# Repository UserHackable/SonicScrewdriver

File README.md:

## LiPolyRGB 

### Board dimensions

* (160000, 70000) original units
* (1.6000, 0.7000) inches
* (40.6400, 17.7800) mm

| Front | Back |
| --- | --- |
|  |  |

## LiPolySonicScrewdriver 

### Board dimensions

* (190000, 47500) original units
* (1.9000, 0.4750) inches
* (48.2600, 12.0650) mm

| Front | Back |
| --- | --- |
|  |  |

## sonic_screwdriver 

### Board dimensions

* (139950, 29960) original units
* (1.3995, 0.2996) inches
* (35.5473, 7.6098) mm

| Front | Back |
| --- | --- |
|  |  |

## sonic_screwdriver_lipo 

### Board dimensions

* (139950, 29960) original units
* (1.3995, 0.2996) inches
* (35.5473, 7.6098) mm

| Front | Back |
| --- | --- |
|  |  |

## SonicScrewdriverThru 

### Board dimensions

* (249951, 49961) original units
* (2.4995, 0.4996) inches
* (63.4876, 12.6901) mm

| Front | Back |
| --- | --- |
|  |  |

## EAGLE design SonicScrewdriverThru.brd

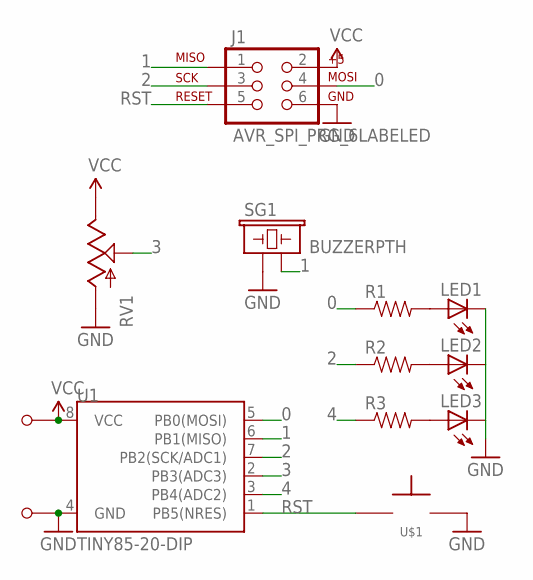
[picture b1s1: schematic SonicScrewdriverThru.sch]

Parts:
J1: AVR_SPI_PRG_6LABELED; 2X3-NS
LED1, LED2, LED3: LEDOVAL; LED-OVAL
R1, R2, R3: RESISTORAXIAL-0.3; AXIAL-0.3
RV1: POTTHUMB; THUMB
SG1: BUZZERPTH; BUZZER-12MM
U1: TINY85-20-DIP; DIP08
U$1: TAC_SPST_NO
U$2, U$3: M1; M1_NO_STRAIN

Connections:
0: J1.4, R1.P$1 (1), U1.5 (PB0(MOSI))
1: J1.1, SG1.- (2), U1.6 (PB1(MISO))
2: J1.3, R2.P$1 (1), U1.7 (PB2(SCK/ADC1))
3: RV1.B (S), U1.2 (PB3(ADC3))
4: R3.P$1 (1), U1.3 (PB4(ADC2))
GND: J1.6, LED1.CATHODE (C), LED2.CATHODE (C), LED3.CATHODE (C), RV1.A, SG1.+ (1), U1.4 (GND), U$1.P$2, U$3.P$1
unnamed: LED1.ANODE (A), R1.P$2 (2)
unnamed: LED2.ANODE (A), R2.P$2 (2)
unnamed: LED3.ANODE (A), R3.P$2 (2)
RST: J1.5, U1.1 (PB5(NRES)), U$1.P$1
VCC: J1.2, RV1.C (E), U1.8 (VCC), U$2.P$1

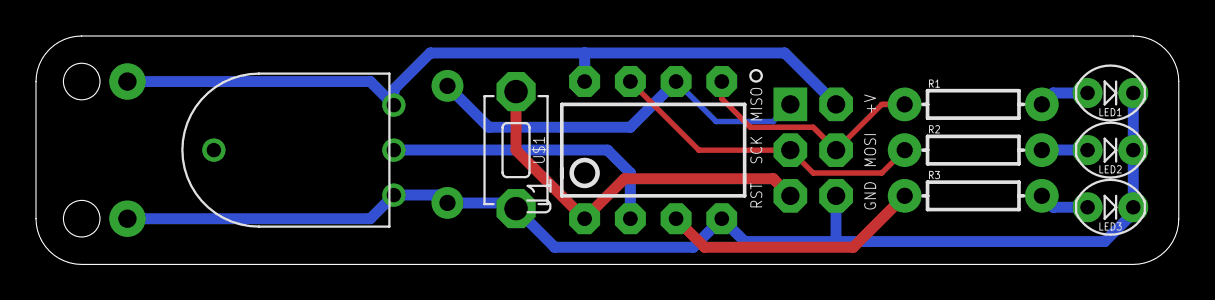
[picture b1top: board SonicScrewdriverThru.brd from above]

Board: 2 copper layers, 63.5 x 12.7 mm, 13 parts (1 on the bottom side), 11 nets.

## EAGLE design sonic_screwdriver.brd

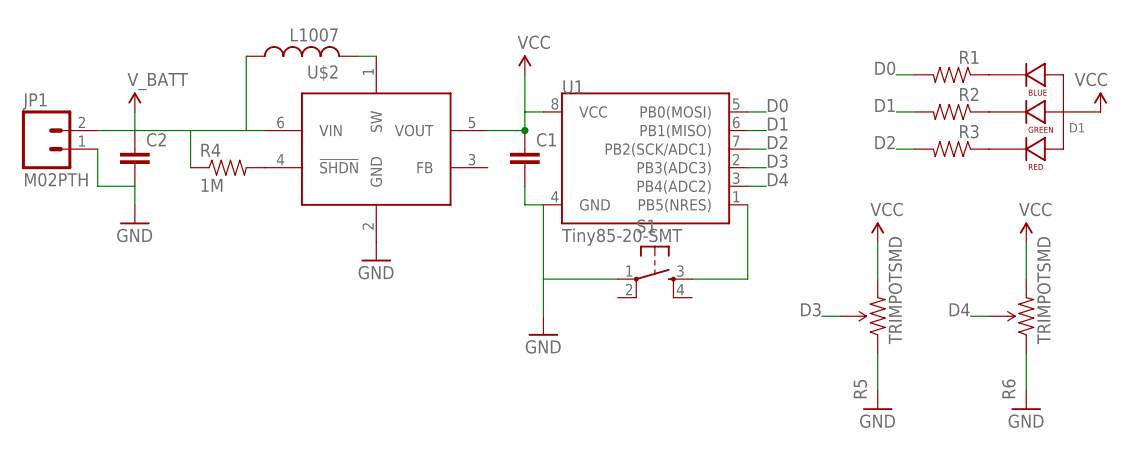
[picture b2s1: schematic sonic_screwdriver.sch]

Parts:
C1, C2: CAP1206; 1206
D1: LED-RGB-CA-THRUEDGE; LED-RGB-EDGE
JP1: M02PTH; 1X02
R1, R2, R3: RESISTOR0805-RES; 0805
R4: 1M; 0805
R5, R6: TRIMPOTSMD; TRIMPOT-3MM
S1: TAC_SWITCHSMD; TACTILE-SWITCH-SMD
U1: Tiny85-20-SMT; SO08-EIAJ
U$1: AAT1217; TSOT-23-6
U$2: L1007

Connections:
D0: R1.2, U1.5 (PB0(MOSI))
D1: R2.2, U1.6 (PB1(MISO))
D2: R3.2, U1.7 (PB2(SCK/ADC1))
D3: R5.2 (WIPER), U1.2 (PB3(ADC3))
D4: R6.2 (WIPER), U1.3 (PB4(ADC2))
GND: C1.2, C2.2, JP1.1, R5.1 (CCW), R6.1 (CCW), S1.1, U1.4 (GND), U$1.2 (GND)
unnamed: D1.4 (BLUE_CATHODE), R1.1
unnamed: D1.3 (GREEN_CATHODE), R2.1
unnamed: D1.1 (RED_CATHODE), R3.1
unnamed: R4.2, U$1.4 (!SHDN)
unnamed: U$1.1 (SW), U$2.P$2 (2)
RESET: S1.3, U1.1 (PB5(NRES))
VCC: C1.1, D1.2 (ANODE), R5.3 (CW), R6.3 (CW), U1.8 (VCC), U$1.5 (VOUT)
V_BATT: C2.1, JP1.2, R4.1, U$1.6 (VIN), U$2.P$1 (1)

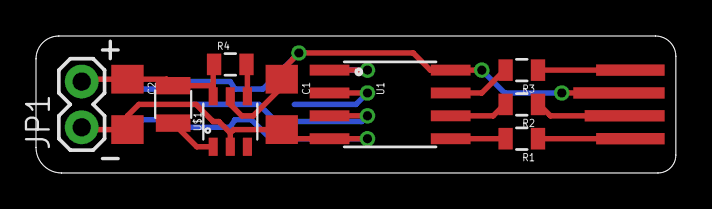
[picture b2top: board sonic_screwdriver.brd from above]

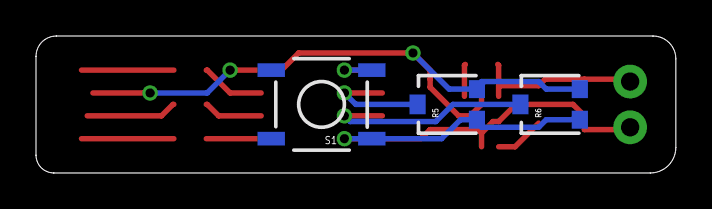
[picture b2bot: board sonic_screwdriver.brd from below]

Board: 2 copper layers, 35.5 x 7.6 mm, 14 parts (3 on the bottom side), 14 nets.

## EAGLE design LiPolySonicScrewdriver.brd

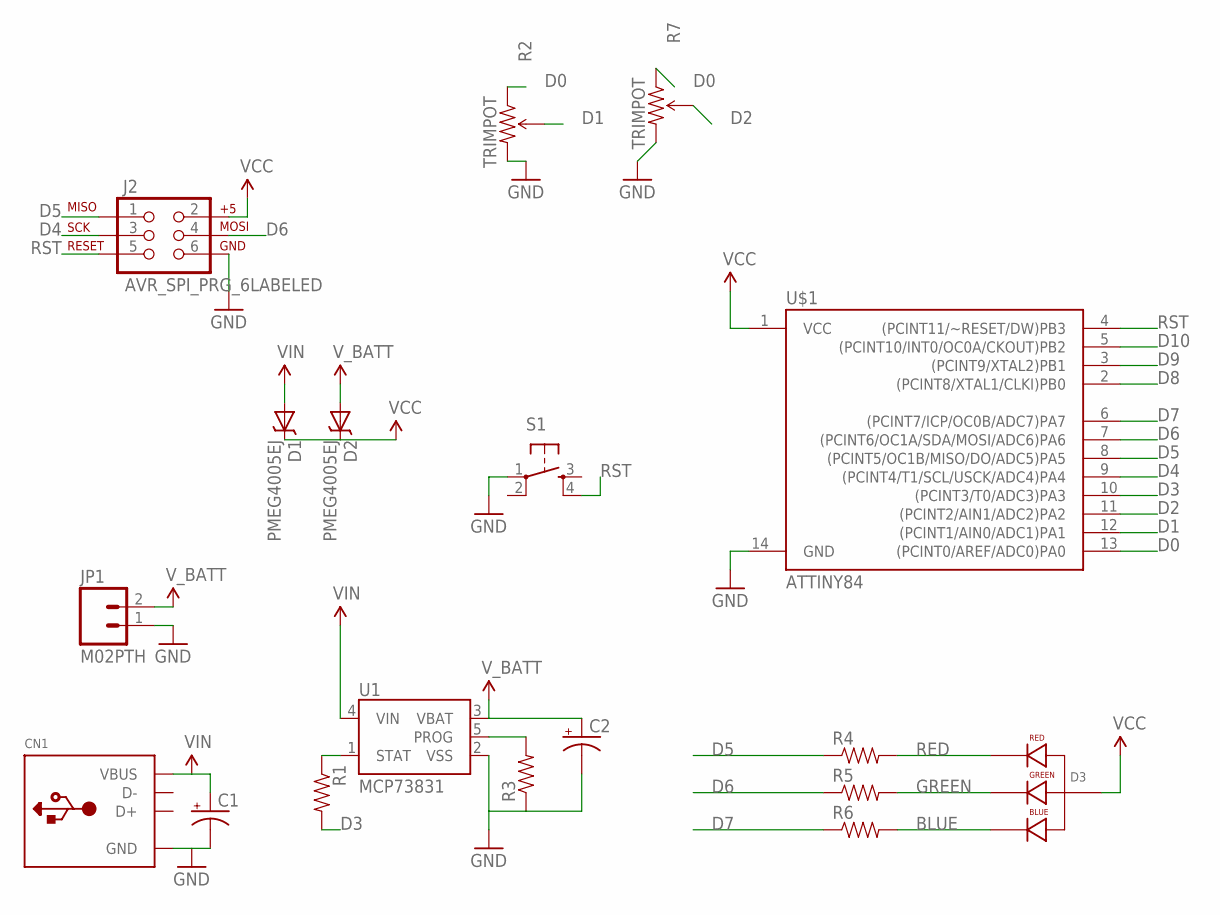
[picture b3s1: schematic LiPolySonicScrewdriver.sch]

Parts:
C1, C2: CAP_POL1206; EIA3216
CN1: USB_TYPEAPCB; USBA_PCB
D1, D2: PMEG4005EJ; SOD-323
D3: LED-RGB-CA-THRUEDGE; LED-RGB-EDGE
J2: AVR_SPI_PRG_6LABELED; 2X3-NS
JP1: M02PTH; 1X02
R1, R3: RESISTOR0805-RES; 0805
R2, R7: TRIMPOT; TRIMPOT-5MM-V2
R4, R5, R6: RESISTOR1206; 1206
S1: TAC_SWITCHSMD; TACTILE-SWITCH-SMD
U1: MCP73831; SOT23-5
U$1: ATTINY84; SO14

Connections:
BLUE: D3.4 (BLUE_CATHODE), R6.2
D0: R2.A (CCW), R7.A (CCW), U$1.13 ((PCINT0/AREF/ADC0)PA0)
D1: R2.B (WIPER), U$1.12 ((PCINT1/AIN0/ADC1)PA1)
D2: R7.B (WIPER), U$1.11 ((PCINT2/AIN1/ADC2)PA2)
D3: R1.2, U$1.10 ((PCINT3/T0/ADC3)PA3)
D4: J2.3, U$1.9 ((PCINT4/T1/SCL/USCK/ADC4)PA4)
D5: J2.1, R4.1, U$1.8 ((PCINT5/OC1B/MISO/DO/ADC5)PA5)
D6: J2.4, R5.1, U$1.7 ((PCINT6/OC1A/SDA/MOSI/ADC6)PA6)
D7: R6.1, U$1.6 ((PCINT7/ICP/OC0B/ADC7)PA7)
D8: U$1.2 ((PCINT8/XTAL1/CLKI)PB0)
D9: U$1.3 ((PCINT9/XTAL2)PB1)
D10: U$1.5 ((PCINT10/INT0/OC0A/CKOUT)PB2)
GND: C1.C (-), C2.C (-), CN1.GND, J2.6, JP1.1, R2.C (CW), R3.1, R7.C (CW), S1.1, U1.2 (VSS), U$1.14 (GND)
GREEN: D3.3 (GREEN_CATHODE), R5.2
unnamed: R3.2, U1.5 (PROG)
RED: D3.1 (RED_CATHODE), R4.2
RST: J2.5, S1.4, U$1.4 ((PCINT11/~RESET/DW)PB3)
STAT: R1.1, U1.1 (STAT)
VCC: D1.C, D2.C, D3.2 (ANODE), J2.2, U$1.1 (VCC)
VIN: C1.A (+), CN1.VCC (VBUS), D1.A, U1.4 (VIN)
V_BATT: C2.A (+), D2.A, JP1.2, U1.3 (VBAT)

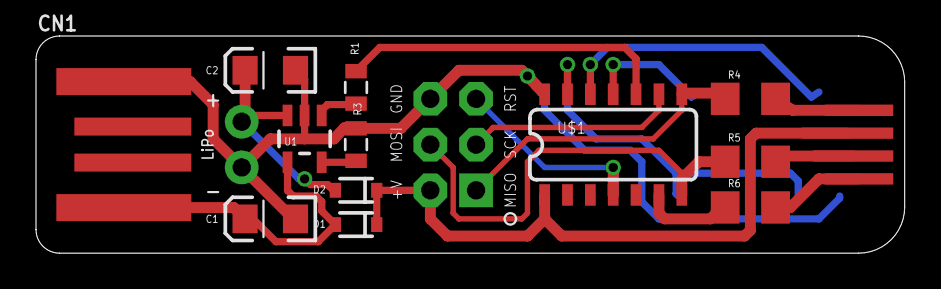
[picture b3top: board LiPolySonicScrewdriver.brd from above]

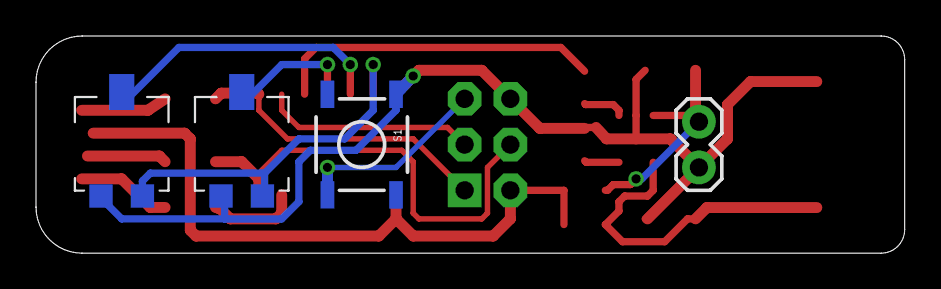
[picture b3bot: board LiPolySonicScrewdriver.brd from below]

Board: 2 copper layers, 48.3 x 12.1 mm, 18 parts (4 on the bottom side), 18 nets.

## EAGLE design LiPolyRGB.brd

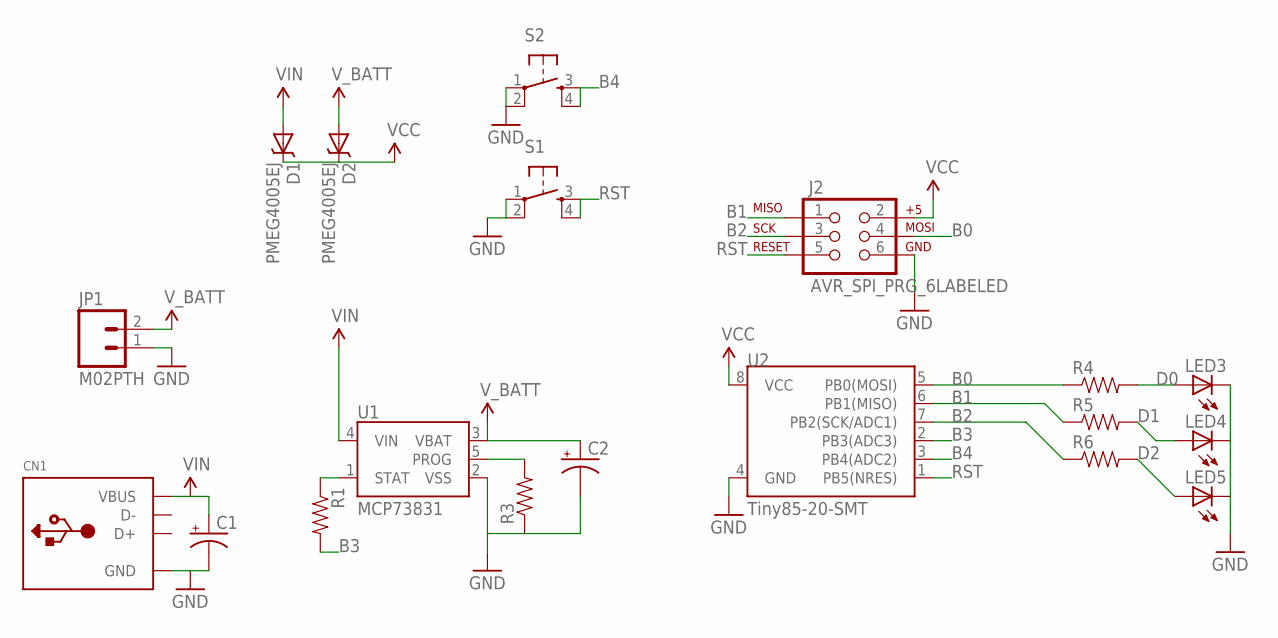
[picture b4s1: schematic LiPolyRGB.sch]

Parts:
C1, C2: CAP_POL1206; EIA3216
CN1: USB_TYPEAPCB; USBA_PCB
D1, D2: PMEG4005EJ; SOD-323
J2: AVR_SPI_PRG_6LABELED; 2X3-NS
JP1: M02PTH; 1X02
LED3, LED4, LED5: LEDOVAL_EDGE; LED-OVAL-EDGE
R1, R3, R4, R5, R6: RESISTOR0805-RES; 0805
S1, S2: TAC_SWITCHSMD; TACTILE-SWITCH-SMD
U1: MCP73831; SOT23-5
U2: Tiny85-20-SMT; SO08-EIAJ

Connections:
B0: J2.4, R4.1, U2.5 (PB0(MOSI))
B1: J2.1, R5.1, U2.6 (PB1(MISO))
B2: J2.3, R6.1, U2.7 (PB2(SCK/ADC1))
B3: R1.2, U2.2 (PB3(ADC3))
B4: S2.3, S2.4, U2.3 (PB4(ADC2))
D0: LED3.ANODE (A), R4.2
D1: LED4.ANODE (A), R5.2
D2: LED5.ANODE (A), R6.2
GND: C1.C (-), C2.C (-), CN1.GND, J2.6, JP1.1, LED3.CATHODE (C), LED4.CATHODE (C), LED5.CATHODE (C), R3.1, S1.1, S1.2, S2.1, S2.2, U1.2 (VSS), U2.4 (GND)
unnamed: R3.2, U1.5 (PROG)
RST: J2.5, S1.3, S1.4, U2.1 (PB5(NRES))
STAT: R1.1, U1.1 (STAT)
VCC: D1.C, D2.C, J2.2, U2.8 (VCC)
VIN: C1.A (+), CN1.VCC (VBUS), D1.A, U1.4 (VIN)
V_BATT: C2.A (+), D2.A, JP1.2, U1.3 (VBAT)

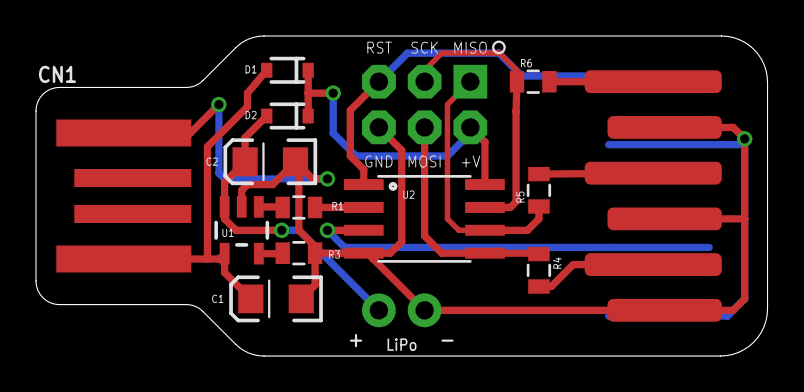
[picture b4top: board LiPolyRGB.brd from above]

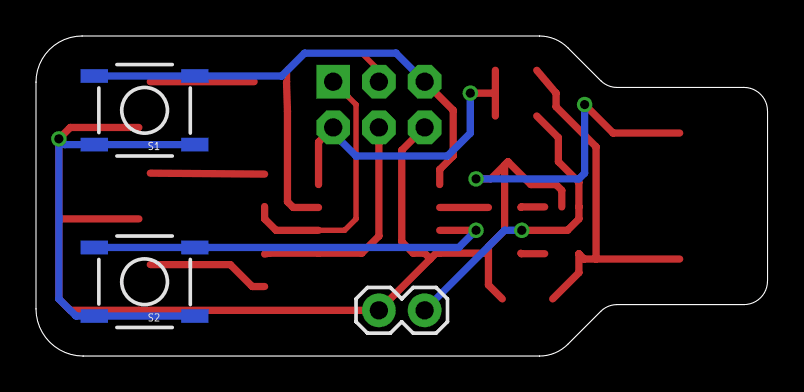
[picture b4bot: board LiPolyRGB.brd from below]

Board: 2 copper layers, 40.6 x 17.8 mm, 19 parts (3 on the bottom side), 15 nets.

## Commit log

2016-04-08 from Makefile

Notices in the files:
parts and their libraries:
SparkFun-PowerIC: Licensing: Creative Commons ShareAlike 4.0 International - https://creativecommons.org/licenses/by-sa/4.0
